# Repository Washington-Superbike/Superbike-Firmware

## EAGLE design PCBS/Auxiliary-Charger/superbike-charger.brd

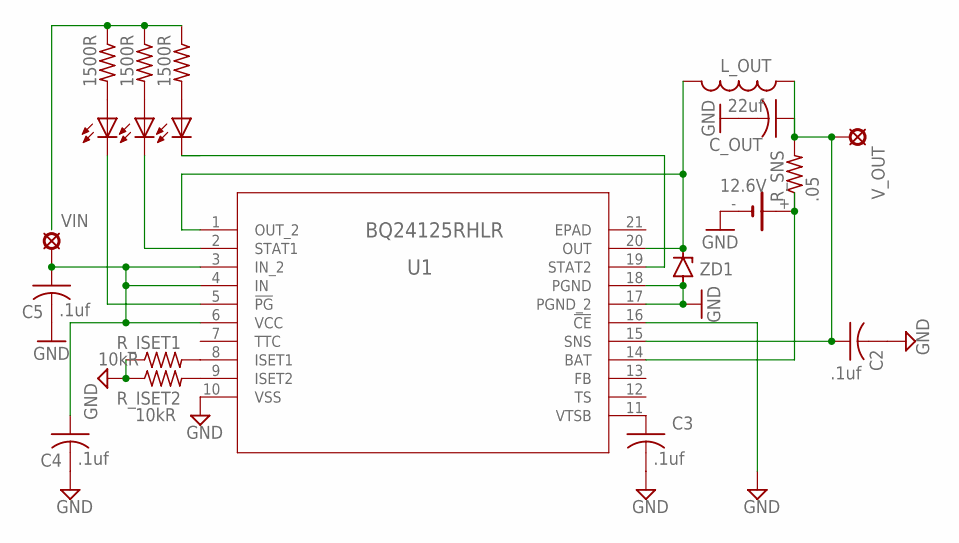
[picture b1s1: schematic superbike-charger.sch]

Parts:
12.6V: SL340P; SL-340/P3.6V
C2, C3, C4, C5: .1uf; C0805
C_OUT: 22uf; C0805
LED1, LED2, LED3: LED; SMARTLED-TTW
L_OUT: L-USL3216C; L3216C
RSYS1, RSYS2, RSYS3: 1500R; R0805
R_ISET1, R_ISET2: 10kR; R0805
R_SNS: .05; R0402
U1: BQ24125RHLR; RHL20_2P05X3P05
VIN: LSP13
V_OUT: LSP13
ZD1: BZX55; DO35Z10

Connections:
GND: 12.6V.-, C2.2, C3.2, C4.2, C5.2, C_OUT.2, R_ISET1.1, R_ISET2.1, U1.10 (VSS), U1.16 (!CE)
unnamed: L_OUT.2, U1.1 (OUT_2), U1.20 (OUT), ZD1.C
unnamed: U1.17 (PGND_2), U1.18 (PGND), ZD1.A
unnamed: C2.1, C_OUT.1, L_OUT.1, R_SNS.2, U1.15 (SNS), V_OUT.MP
unnamed: R_ISET1.2, U1.8 (ISET1)
unnamed: R_ISET2.2, U1.9 (ISET2)
unnamed: 12.6V.+, R_SNS.1, U1.14 (BAT)
unnamed: C3.1, U1.11 (VTSB)
unnamed: C4.1, C5.1, U1.3 (IN_2), U1.4 (IN), U1.6 (VCC), VIN.MP
unnamed: LED1.C@1 (C), U1.2 (STAT1)
unnamed: LED2.C@1 (C), U1.19 (STAT2)
unnamed: LED3.C@1 (C), U1.5 (!PG)
unnamed: RSYS1.1, RSYS2.1, RSYS3.1
unnamed: LED3.A@1 (A), RSYS1.2
unnamed: LED1.A@1 (A), RSYS2.2
unnamed: LED2.A@1 (A), RSYS3.2

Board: 2 copper layers, 20 parts (0 on the bottom side), 16 nets, no tracks yet.

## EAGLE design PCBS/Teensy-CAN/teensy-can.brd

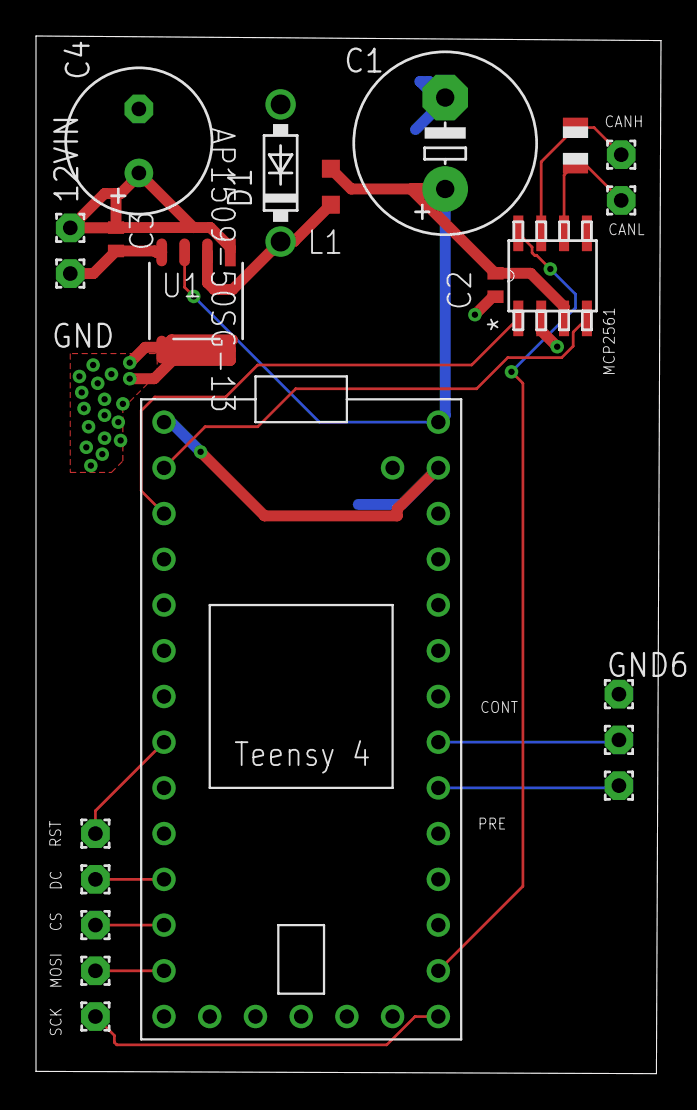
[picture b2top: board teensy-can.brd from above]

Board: 2 copper layers, 34.7 x 57.6 mm, 22 parts (0 on the bottom side), 16 nets.

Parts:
12VIN: 1,6/0,8
120R: R0805
C1: 1000uF; E5-10,5
C2, C3: 0.1uF; C0402
C4: 330uF; E3,5-8
CAN_H: 1,6/0,8
CAN_L: 1,6/0,8
CONTACT-RL: 1,6/0,8
D1: 1N5817-T; DO41-7.6
GND, GND6: 1,6/0,8
L1: 33uH; L2012C
MOSI: 1,6/0,8
PRECHRG-RLY: 1,6/0,8
SCK: 1,6/0,8
TFT_CS: 1,6/0,8
TFT_DC: 1,6/0,8
TFT_RST: 1,6/0,8
U1: AP1509-50SG-13; SOP-8L_DIO
U$1: MCP2551-X/SN; SOIC8-N_MC
U$2: TEENSY4.0

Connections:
5VIN: C1.+, C2.1, L1.2, U1.3, U$1.3, U$2.VIN
12VIN: 12VIN.1, C3.1, C4.+, U1.1
CANRX: U$1.4, U$2.D0
CANTX: U$1.1, U$2.D1
GND: C1.-, C2.2, C3.2, C4.-, D1.A, GND.1, GND6.1, U1.4, U1.5, U1.6, U1.7, U1.8, U$1.2, U$2.AGND, U$2.GND@1, U$2.GND@2
MOSI: MOSI.1, U$2.D11
unnamed: PRECHRG-RLY.1, U$2.D18/A4
unnamed: CONTACT-RL.1, U$2.D19/A5
unnamed: TFT_RST.1, U$2.D6
unnamed: U$1.8, U$2.D14/A0
unnamed: 120R.1, CAN_H.1, U$1.7
unnamed: 120R.2, CAN_L.1, U$1.6
unnamed: SCK.1, U$2.D13/LED
OUTPUT: D1.C, L1.1, U1.2
TFT_CS: TFT_CS.1, U$2.D10
TFT_DC: TFT_DC.1, U$2.D9

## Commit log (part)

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2020-10-01 pcbs
2020-10-01 firmware 1st
2020-10-02 Adding DC-DC to control board. UNFINISHED
2020-10-02 more dc-dc adds
2020-11-05 teensy board final draft
2021-02-12 charger and board changes, adding firmware soon
2021-02-17 Reorganizing code
2021-02-17 testing to show merge
2021-02-17 testing again for merge
2021-02-17 testing merge conflict
2021-02-17 fixing merge errors
2021-02-19 still need to fix importing error with flexcan
2021-02-19 different files for separate tasks, compiles
2021-02-23 redesign and pre-charge separated
2021-02-23 defining can bus / display shared data
2021-02-23 display branch
2021-02-24 changing structs for CAN
2021-02-24 compiling with motor controller can definitions
2021-02-26 adding data logging for sd card
2021-02-26 Added CAN bus Structs, series_voltage function, moved .h macros
2021-02-26 added data logging and required libraries
2021-02-26 data logging sd test
2021-02-26 adding logging capability, haven't implemented the actual writing/saving/opening of the log files; add a buffer to only write when we need to save --> future
2021-02-26 added SD card functionality, data logging task (no timer yet)
2021-02-26 ready to test sd card, need to modify board jumpers to allow 3.3v instead of 5v
2021-02-26 moving commits to datalogging, not working version of struct implementation
2021-02-27 fixed struct issue, just use maximum length of buffer
2021-02-27 added data logging, fixed structure issues in PreCharge and CAN bus
2021-02-28 Corrected Parenthesis in decodeMotorStats/decodeMotorTemps, decipher BMSStatus now has BMSStatus parameter
2021-02-28 Moved ISR setup functions to correct files
2021-02-28 Created Scheduler file for ISR flags and implementation
2021-02-28 Separated PreChargeCircuitFSM function into two functions for Transition actions and State actions
2021-03-01 setupCAN bug lol
2021-03-01 working version, dataLogging + can bus work as expected
2021-03-04 Precharge functions use Structs, functions ready to test
2021-03-05 Previous Commit, but compiles
2021-03-05 Created function initializeCANStruts in Main
2021-03-05 function setupCAN also calls setupCANISR, case DD_BMS_STATUS_IND bmsStatus changed to canData.bmsStatus
2021-03-05 Added function declarations of Scheduler.ino to Scheduler.h
2021-03-05 Added function declarations in Precharge.ino to Precharge.h
2021-03-05 Precharge functions now only use struct PrechargeTaskData without struct MotorStats
2021-03-05 Made screen struct, made more methods in Display
2021-03-08 Update Display. Digits update independently
2021-03-08 testing display
2021-03-14 Wrote pin definitions for buttons used for precharging in Precharge.h, Updated preChargeCircuitFSMTransitionActions to use contactor_close_button and high_voltage_toggle
2021-03-15 Implemented function for checking when motorcontroller is pre-charged
2021-03-15 preChargeCircuitFSMTransitionActions now updates LEDs: CONTACTOR_PRECHARGED_LED and CONTACTOR_CLOSED_LED
2021-03-15 Renamed preChargeCheck function to preChargeFSMCheck
2021-04-08 Precharge initialized
2021-04-10 slow and fast ISRs implemented
2021-04-12 added print, data logging running more than once a second
2021-04-14 Testing screen loaded in
2021-04-14 fixed 117 in main, was doing == instead of =
2021-04-15 implemented new function closeContactor for PreCharging
2021-04-22 Changed CAN.ino pointer address are set to value addresses, not values
2021-04-22 update to method closeContactor()
2021-04-23 last changes after testing with the BMS
2021-04-27 after testing changes
2021-05-22 sd card working, display is displaying blank values
2021-05-23 PRE-CHARGE TESTED F YEAH
2021-05-27 SoC skeleton
2021-05-27 SOC functions written
2021-06-04 added simpsons rule to soc
2021-06-05 charger/evcc messages + displayed on screen
2021-06-05 SoC algorithm implmented for discharging currents -- code does not compile :(
2021-06-05 charger tested, teensy has issue when charger is on the CAN bus
2022-02-15 soc branch init
2022-09-03 Main FW: small clean-up changes
    Mostly style changes / unused variables removed. One of the can decoding
    functions was using pointers to the buffer instead of the dereferenced
    values.
2022-09-03 Main FW: improve data logging for float vs int
    The previous data logging scheme was really clunky, this improves it
    and also makes it easier to adopt other printing types in the future
2022-09-03 Main FW: small clean-up changes
    Mostly style changes / unused variables removed. One of the can
    decoding functions was using pointers to the buffer instead of the dereferenced values.
2022-09-04 Main FW: Added basic FreeRTOS, untested currently
    Basic import of a Teensy4 FreeRTOS library
    Modified tasks to use FreeRTOS
    Cleaned up unnecessary files for the display
2022-09-04 Main FW: improve RTOS tasks, Precharge logic
    The precharge firmware was not very clean. It still needs some work done
    but should be easier to follow now.
    Made the RTOS tasks enter loops so that they will execute properly.
2022-09-10 Main FW: remove old PCB files
    Since we moved to Altium, these PCB files are
    unnecessary
2022-09-30 Main FW: Define RTOS task stack sizes, basic testing
    The display task + datalogging should have a larger stack size as they
    need underlying tft and sd card data buffers. Some basic testing was
    done without being connected to the larger system.
2022-09-30 RTOS: add SPI mutex to avoid bus conflicts
    Bus conflicts were occuring in SPI between the display and datalog task.
    The mutex now provides safe access to the bus.
2022-10-01 Datalog: Save files every 1 second
    Before we were assuming that the task would for sure run 20 times a
    second. This is not 100% guaranteed due to the new mutex, so we should
    save based on the clock instead.
2022-10-11 Sorted Display mapping
2022-11-25 Blink
2022-11-25 Pico Blink
2022-11-28 teensy RTC not working, board is asking for sync from pc every reset instead of using the RTC from VBAT
2022-12-01 Sorted 4.0 display integration with RTOS
2022-12-01 removed some spare comments
2022-12-01 added PCBs
2022-12-01 merged display changes and added aux battery changes that Trevor made too
2022-12-01 quick pin fix in display.h
2022-12-01 one last time?
2022-12-07 Sorted all display changes to 4.1, Chase feel free to add all comments as needed
2022-12-10 fast display working, don't see any crashing at the moment
2022-12-16 Add config.h, restructure/name Precharge.ino
    config.h will allow us to change the compilation of the FW based on
    user-defined settings.
    Renamed PC_STATE -> HV_STATE for clarity, as well as
    closeContactor->isHVSafe.
    Added some comments throughout the code and did some auto-formatting (CTRL-T)
2023-02-08 Pushing latest display integration. This should have proper erasure and have display fully optimized for debugging. Next step is to integrate the speedometer for display and then display is done.
2023-02-10 Added speedometer, added bunch of TODOs to implement angle kill switch
2023-02-10 Gyroscope code
    Added variables relevant to the gyroscope on main.ino. Added <Wire.h>. Added to call a method for angle measuring method on main.ino. Added 4 methods on precharge.ino
2023-03-02 Partial Documentation, but finalized race-ready code
2023-03-03 Documentation 1/3 done. Styling code to properly use the header files fully done.
2023-03-03 Frankly, I'm too tired of doing documentation. Please someone else finish this. I'm gonna sleep
2023-03-03 Everything documented except Can.ino and PreCharge.ino
2023-03-03 No Can.ino or Precharge.ino documentation
2023-03-06 Added another display todo. Sorry lol
2023-03-15 Added Doxygen configuration file into Documentation folder, use this to use Doxygen
2023-03-15 Testing something
2023-03-18 Github tutorial
2023-04-01 Removed enum and some extra variables Change screen with #define instead
2023-04-01 Shortened thermistor printing method a bit
2023-04-01 Slapped config.h back in
2023-04-02 Updated docs
2023-04-18 SOC integration part 1
    Started the integration process
2023-04-18 SOC part 2 update
2023-04-20 Update for speedometer screen
    Added the main battery voltage and made RPM a bit smaller to make room
    for other info. Speed doesn't reprint until it changes.
2023-04-22 update 2
2023-04-25 Added SOC to display
2023-05-02 Display changes
    * Removed enum and some extra variables
    * Shortened thermistor printing method a bit
    * Slapped config.h back in
    Change screen here with #define
    * Update for speedometer screen
    Added the main battery voltage and made RPM a bit smaller to make room
2023-05-03 Updated pin definitions
2023-05-03 Set up stuff for testing a task for mux controls
2023-05-12 Repo: remove unnecessary 'PCBS' directory
    The PCBS directory is very outdated since we moved to Altium
2023-05-12 repo: remove unnecessary documetation files
    Vast majority of our documentation can be done via normal commenting,
    the exceptions can be added in via other means (HTML pages, etc.)
2023-05-23 Restructure Part 1
    The FW has gotten bloated, and needs restructuring.
    First, by using a shared context variable, we can reduce the amount of
    shared pointers to variables.
    Second, we should not be defining any variables in header files, only
    declarations and preprocessor directives.
    Third, we should start removing unnecessary or unclear comments.
2023-05-24 Fixed I2C startup delay to other tasks???
    Moved calibration rotation rate measurements to beginning of prechargeTask. Replaced delay(1) in for loop with vTaskDelay
2023-06-17 using the other FreeRTOS library
2023-06-22 a few functionality changes
    requests/reads battery voltages from BMS, gyro angle check moved
    to error state, and stays in error state until the switch is turned off
2023-06-29 jamming as much stuff as possible on the display
    (gross)
2023-08-05 the c++ agenda
    added some classes in an attempt to make the display stuff a bit
    cleaner...tbh it is not much cleaner but there are fewer #ifdefs and
    templating makes it a bit easier to print non-float variables
2023-08-05 datalogging for other data types
2023-09-27 enable interrupts for receiving CAN messages
2023-09-27 extra angle checks
2023-10-07 test comment
2023-10-18 debug BMS CAN messages for first {x} ms, default at 20s
2024-05-23 Racing Display
2024-05-23 Racing display fixed
2025-03-14 Added BMS Testing Framework
2025-03-15 Update CAN.cpp
    Adding code that initiates the flashing of the error indicator light if an error is detected in the BMS.
2025-03-15 Update CAN.h
    Added the flashERRORLED to CAN.h so we can access it in other files. Also defined ERROR_LED_pin here so we can access without making a new variable everytime.
2025-03-15 Update CAN.h
    Undid the last commit. Wanted to access the the flashErrorLed function from precharge.cpp but can't reference the same global variables as they would have to do it at the same time and the data would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
2025-03-15 Adding code for error indicator light
    Added code for error indicator light. Searching for errors in high voltage and BMS, in the variables bms_status.ltc_fault
    and bms_status.bms_c_fault. Updated version.
2025-03-15 Update PreCharge.cpp
    fixing errors in syntax.
2025-03-15 Update PreCharge.cpp
    Fixed errors and changed to only detect HV errors in this file rather than BMS errors as well.
2025-03-15 Update CAN.h
    small addition.
2025-03-15 Update CAN.cpp
    Small addition
2025-03-15 Update PreCharge.cpp
    small addition
2025-03-15 Update CAN.cpp
    small adjustment.
2025-03-15 Update CAN.h
    Moving variables to global so other file can access them.
2025-03-15 Update PreCharge.cpp
    Removed variables and flashERRORLED function and using the variable and function from CAN.h
2025-03-15 Update CAN.h
    test
2025-03-15 Update CAN.h
    fix test
2025-03-15 Update CAN.cpp
    adding in variables
2025-03-15 Update PreCharge.cpp
    adding in variables
2025-03-15 Update CAN.h
    fix test.
2025-03-16 Update CAN.cpp
    Fixed errors
2025-03-16 Update CAN.h
    Fixed errors
2025-03-16 Update PreCharge.cpp
    Fixed Errors
